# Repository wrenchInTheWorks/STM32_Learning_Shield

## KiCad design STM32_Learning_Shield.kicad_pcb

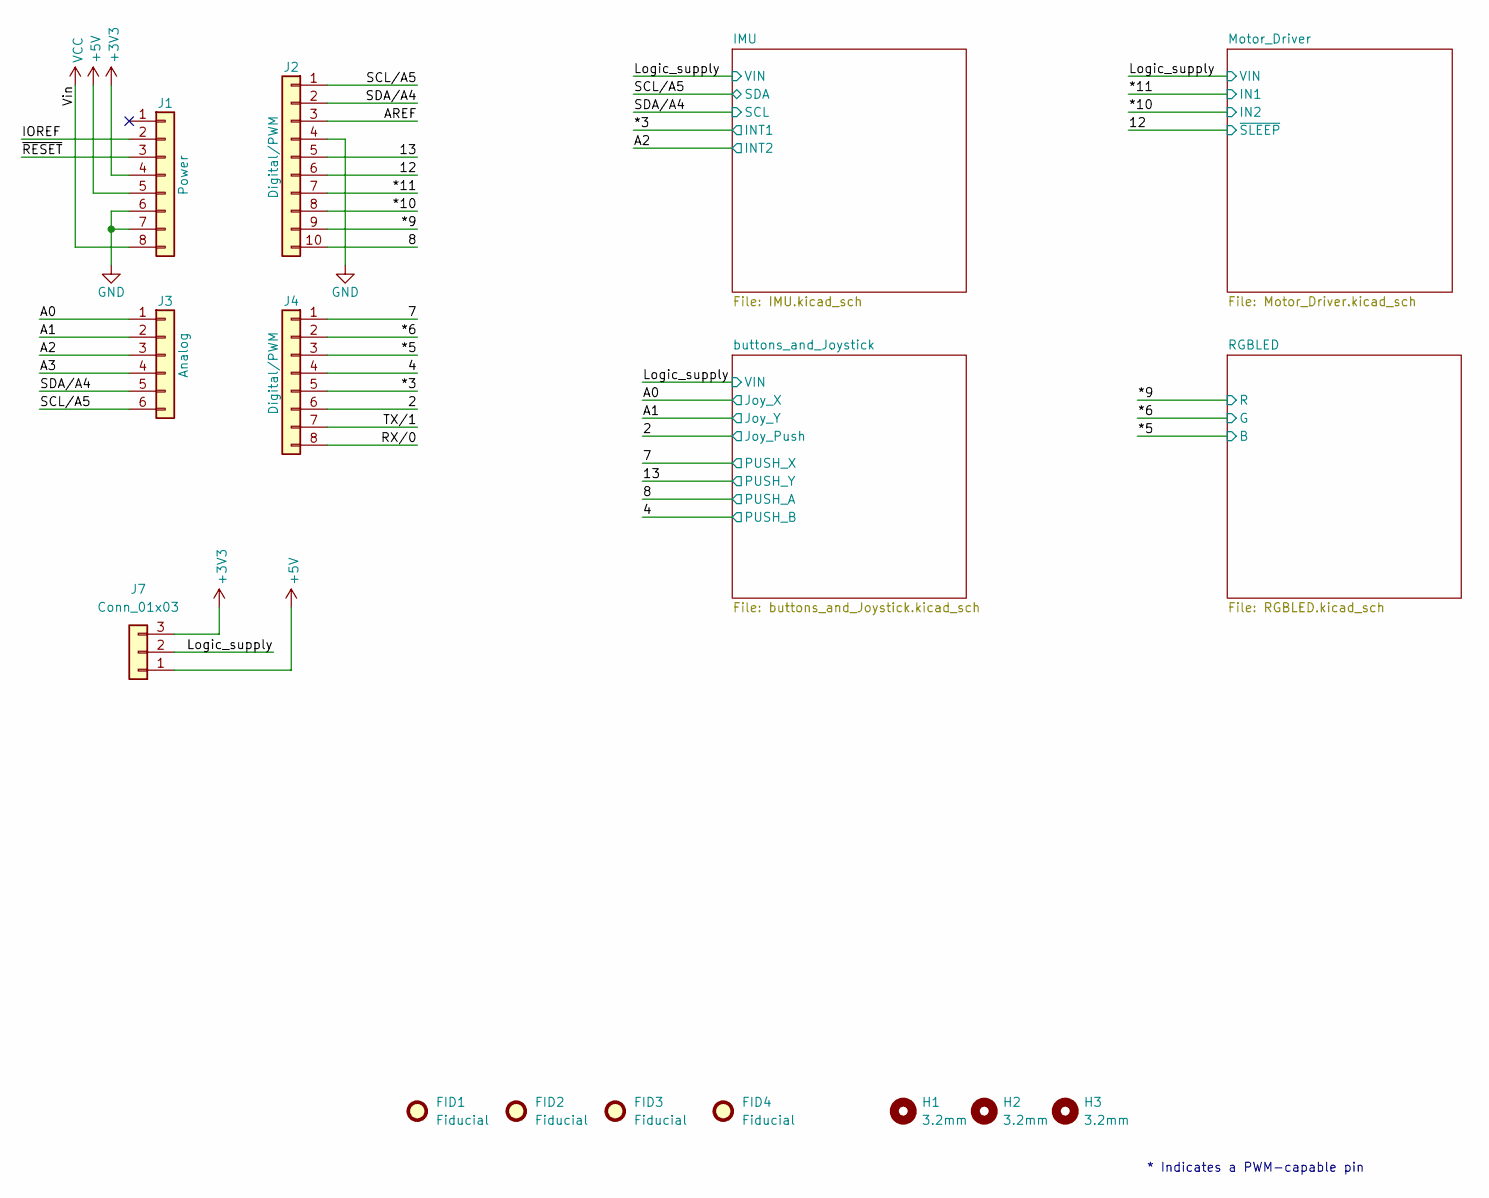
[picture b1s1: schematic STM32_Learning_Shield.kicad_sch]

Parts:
FID1, FID2, FID3, FID4: Fiducial; Fiducial_1mm_Mask3mm
H1, H2, H3: 3.2mm; MountingHole_3.2mm_M3
J1: Power; PinSocket_1x08_P2.54mm_Vertical; MPN PZ254V-11-08P
J2: Digital/PWM; PinSocket_1x10_P2.54mm_Vertical; MPN PZ254V-11-10P
J3: Analog; PinSocket_1x06_P2.54mm_Vertical; MPN HB-PH3-25416PB2GOP
J4: Digital/PWM; PinSocket_1x08_P2.54mm_Vertical; MPN PZ254V-11-08P
J7: Conn_01x03; PinHeader_1x03_P2.54mm_Vertical; MPN 2.54-1*3P

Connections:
+3V3: J1.4, J7.3; also elsewhere on the board
+5V: J1.5, J7.1
/2: J4.6; also elsewhere on the board
/4: J4.4; also elsewhere on the board
/7: J4.1; also elsewhere on the board
/8: J2.10; also elsewhere on the board
/12: J2.6; also elsewhere on the board
/13: J2.5; also elsewhere on the board
/*3: J4.5; also elsewhere on the board
/*5: J4.3; also elsewhere on the board
/*6: J4.2; also elsewhere on the board
/*9: J2.9; also elsewhere on the board
/*10: J2.8; also elsewhere on the board
/*11: J2.7; also elsewhere on the board
/A0: J3.1; also elsewhere on the board
/A1: J3.2; also elsewhere on the board
/A2: J3.3; also elsewhere on the board
/A3: J3.4
/AREF: J2.3
/IOREF: J1.2
/Logic_supply: J7.2; also elsewhere on the board
/RX/0: J4.8
/SCL/A5: J2.1, J3.6; also elsewhere on the board
/SDA/A4: J2.2, J3.5; also elsewhere on the board
/TX/1: J4.7
/~RESET: J1.3
GND: J1.6, J1.7, J2.4; also elsewhere on the board
VCC: J1.8

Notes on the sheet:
* Indicates a PWM-capable pin

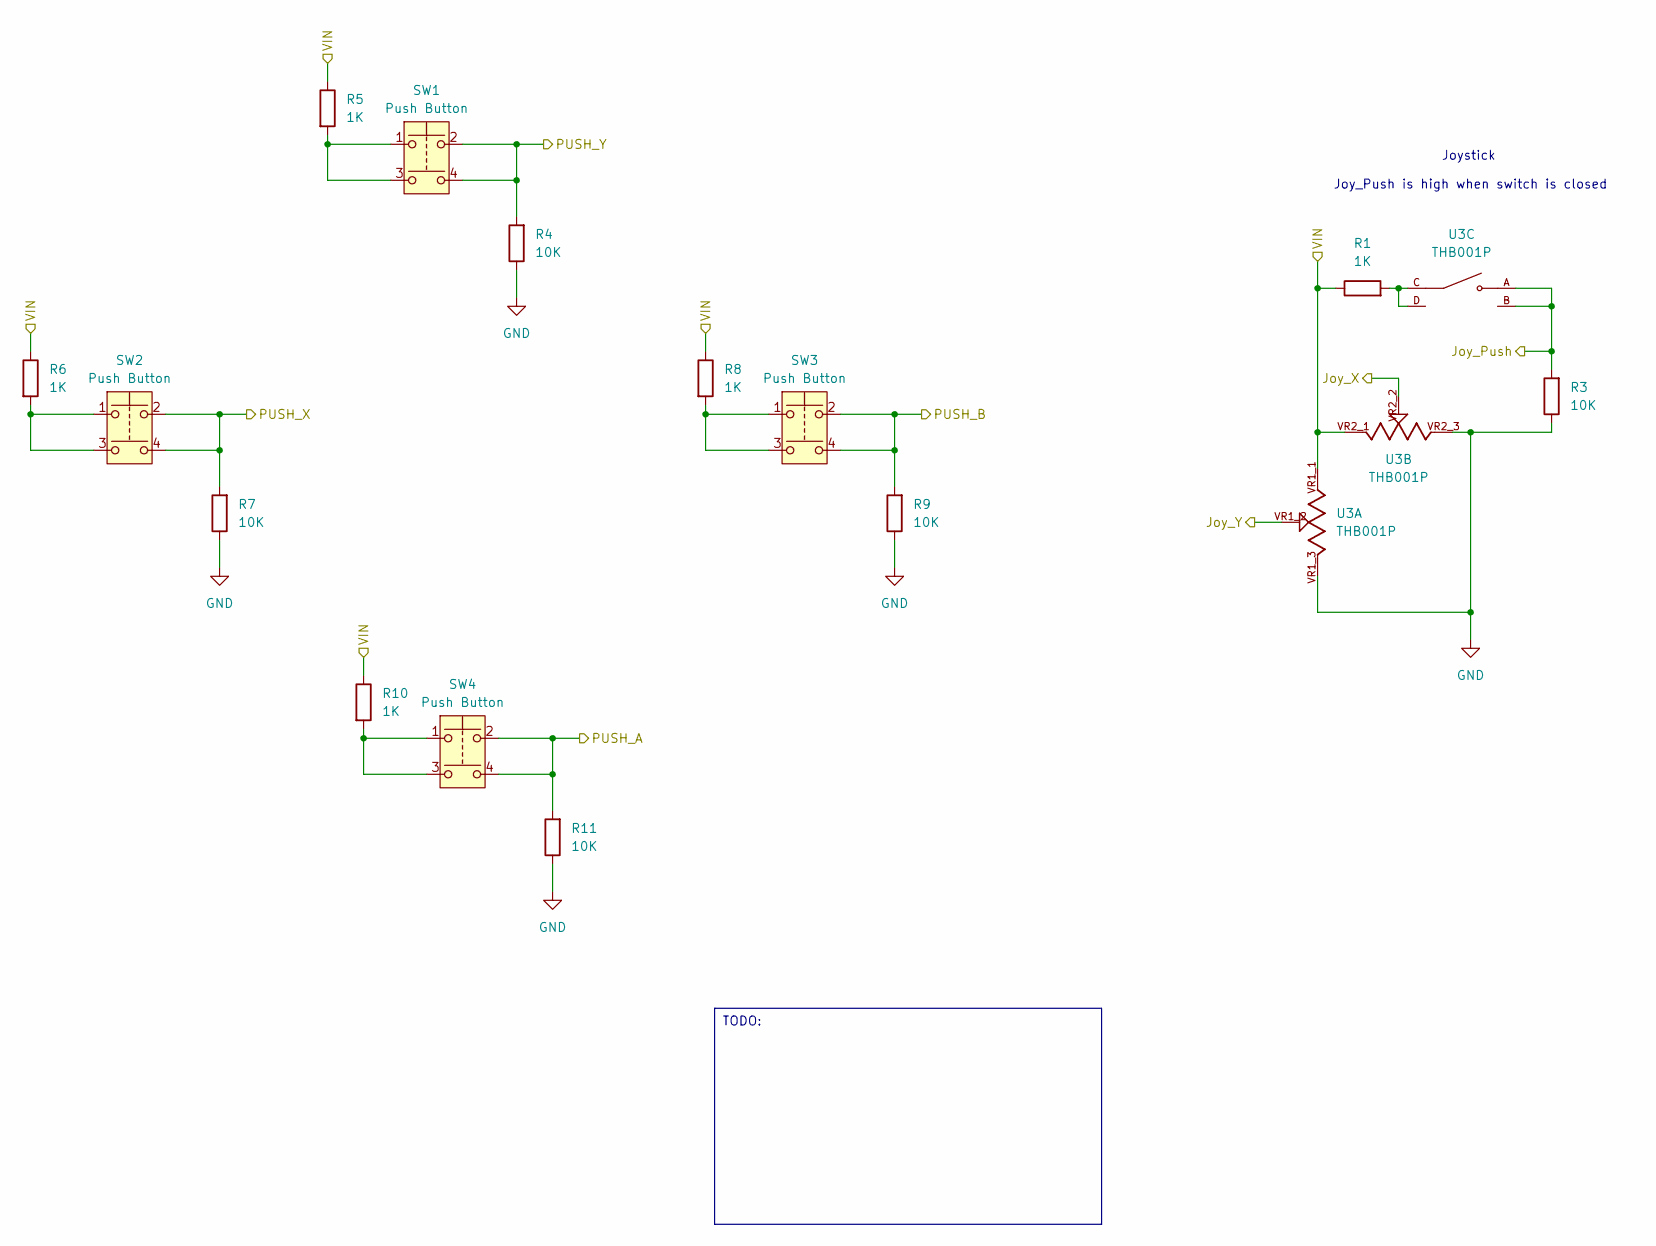
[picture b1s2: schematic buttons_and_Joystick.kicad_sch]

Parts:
R1, R5, R6, R8, R10: 1K; R_0603_1608Metric; MPN 0603WAF1001T5E
R3, R4, R7, R9, R11: 10K; R_0805_2012Metric; MPN 0805W8F1002T5E
SW1, SW2, SW3, SW4: Push Button; SW-TH_4P-L6.0-W6.0-P4.50-LS6.5; MPN TC-00104FB-110E-03
U3: THB001P; CNK_THB001P; PARTREV 27 Jan 22

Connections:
/2: R3.2, U3.A, U3.B; also elsewhere on the board
/4: R9.2, SW3.2, SW3.4; also elsewhere on the board
/7: R7.2, SW2.2, SW2.4; also elsewhere on the board
/8: R11.2, SW4.2, SW4.4; also elsewhere on the board
/13: R4.2, SW1.2, SW1.4; also elsewhere on the board
/A0: U3.VR2_2; also elsewhere on the board
/A1: U3.VR1_2; also elsewhere on the board
/Logic_supply: R1.1, R5.1, R6.1, R8.1, R10.1, U3.VR1_1, U3.VR2_1; also elsewhere on the board
GND: R3.1, R4.1, R7.1, R9.1, R11.1, U3.VR1_3, U3.VR2_3; also elsewhere on the board
unnamed: R1.2, U3.C, U3.D
unnamed: R5.2, SW1.1, SW1.3
unnamed: R6.2, SW2.1, SW2.3
unnamed: R8.2, SW3.1, SW3.3
unnamed: R10.2, SW4.1, SW4.3

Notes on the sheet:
TODO:
Joy_Push is high when switch is closed
Joystick

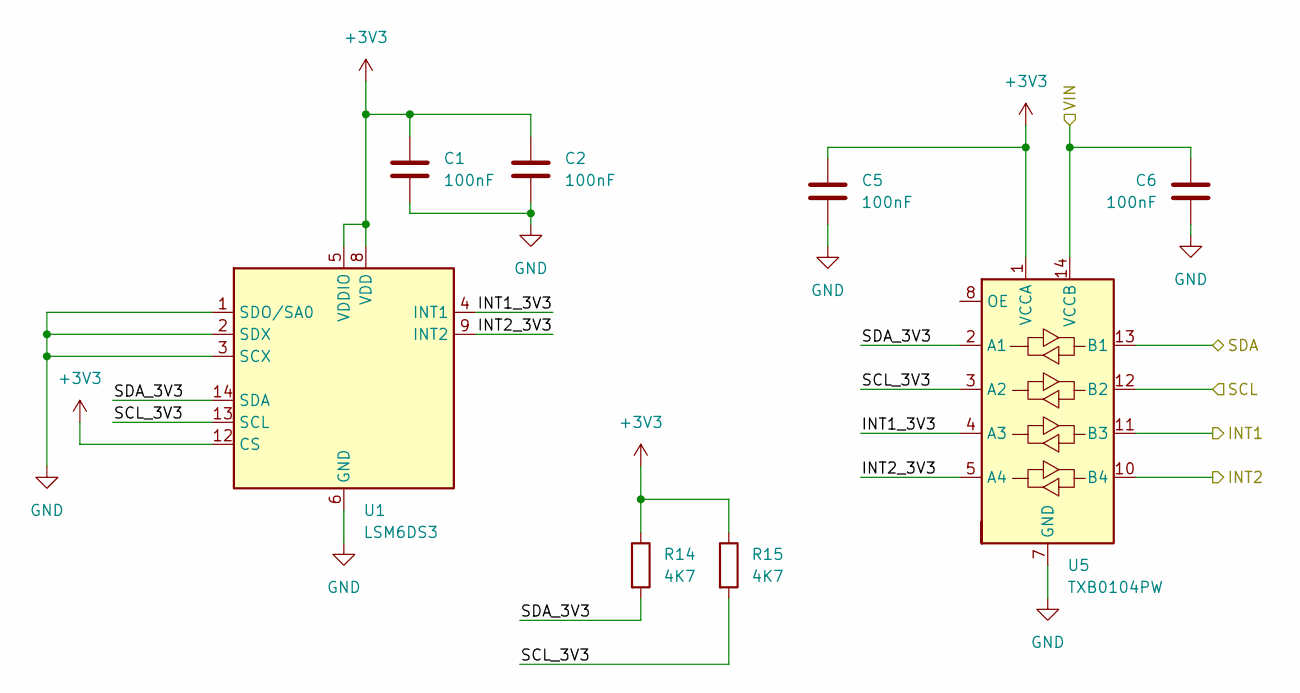
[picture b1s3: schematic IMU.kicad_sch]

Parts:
C1, C2, C5, C6: 100nF; C_0603_1608Metric; MPN CL10B104KB8NNNC
R14, R15: 4K7; R_0603_1608Metric; MPN 0603WAF4701T5E
U1: LSM6DS3; LGA-14_3x2.5mm_P0.5mm_LayoutBorder3x4y; MPN LSM6DS3TR-C
U5: TXB0104PW; SOIC-14_3.9x8.7mm_P1.27mm; MPN TXB0104PWR

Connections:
+3V3: C1.1, C2.1, C5.1, R14.1, R15.1, U1.5 (VDDIO), U1.8 (VDD), U1.12 (CS), U5.1 (VCCA); also elsewhere on the board
/*3: U5.11 (B3); also elsewhere on the board
/A2: U5.10 (B4); also elsewhere on the board
/IMU/INT1_3V3: U1.4 (INT1), U5.4 (A3)
/IMU/INT2_3V3: U1.9 (INT2), U5.5 (A4)
/IMU/SCL_3V3: R15.2, U1.13 (SCL), U5.3 (A2)
/IMU/SDA_3V3: R14.2, U1.14 (SDA), U5.2 (A1)
/Logic_supply: C6.1, U5.14 (VCCB); also elsewhere on the board
/SCL/A5: U5.13 (B1); also elsewhere on the board
/SDA/A4: U5.12 (B2); also elsewhere on the board
GND: C1.2, C2.2, C5.2, C6.2, U1.1 (SDO/SA0), U1.2 (SDX), U1.3 (SCX), U1.6 (GND), U1.7 (GND), U5.7 (GND); also elsewhere on the board

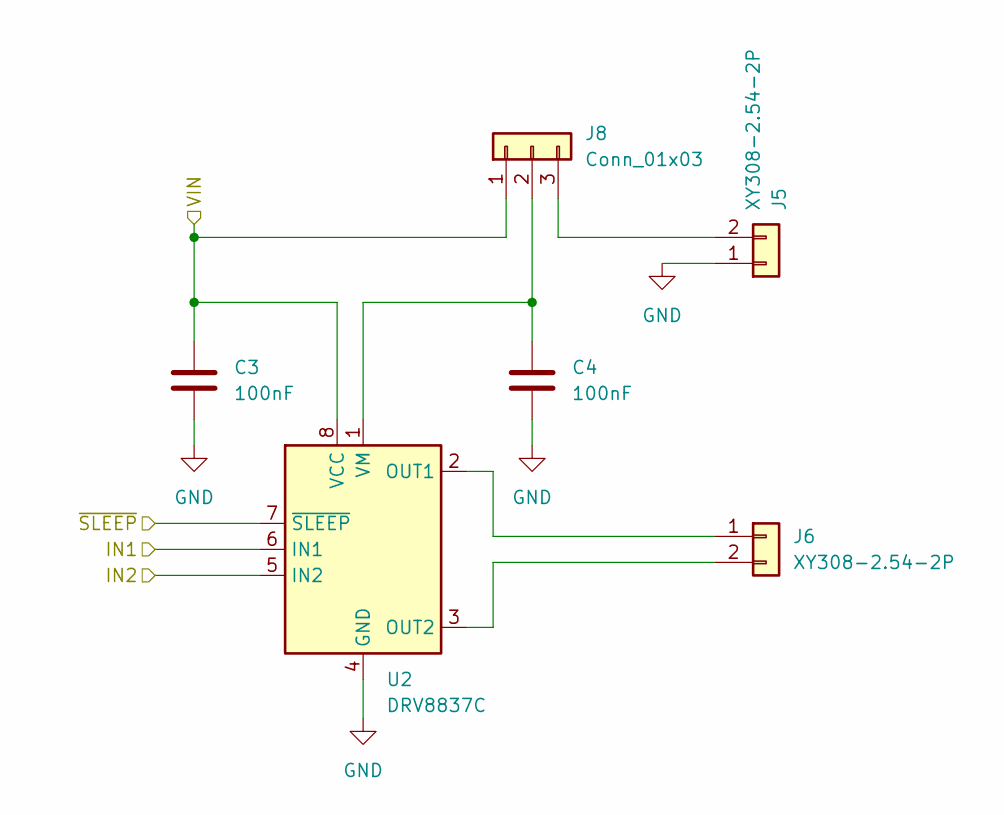
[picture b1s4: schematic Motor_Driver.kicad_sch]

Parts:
C3, C4: 100nF; C_0603_1608Metric; MPN CL10B104KB8NNNC
J5, J6: XY308-2.54-2P; TerminalBlock_Xinya_XY308-2.54-2P_1x02_P2.54mm_Horizontal; MPN XY308-2.54-2P
J8: Conn_01x03; PinHeader_1x03_P2.54mm_Vertical; MPN 2.54-1*3P
U2: DRV8837C; WSON-8-1EP_2x2mm_P0.5mm_EP0.9x1.6mm; MPN DRV8837CDSGR

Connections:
/12: U2.7 (~SLEEP); also elsewhere on the board
/*10: U2.5 (IN2); also elsewhere on the board
/*11: U2.6 (IN1); also elsewhere on the board
/Logic_supply: C3.1, J8.1, U2.8 (VCC); also elsewhere on the board
GND: C3.2, C4.2, J5.1, U2.4 (GND), U2.9 (GND); also elsewhere on the board
unnamed: J5.2, J8.3
unnamed: J6.1, U2.2 (OUT1)
unnamed: J6.2, U2.3 (OUT2)
unnamed: C4.1, J8.2, U2.1 (VM)

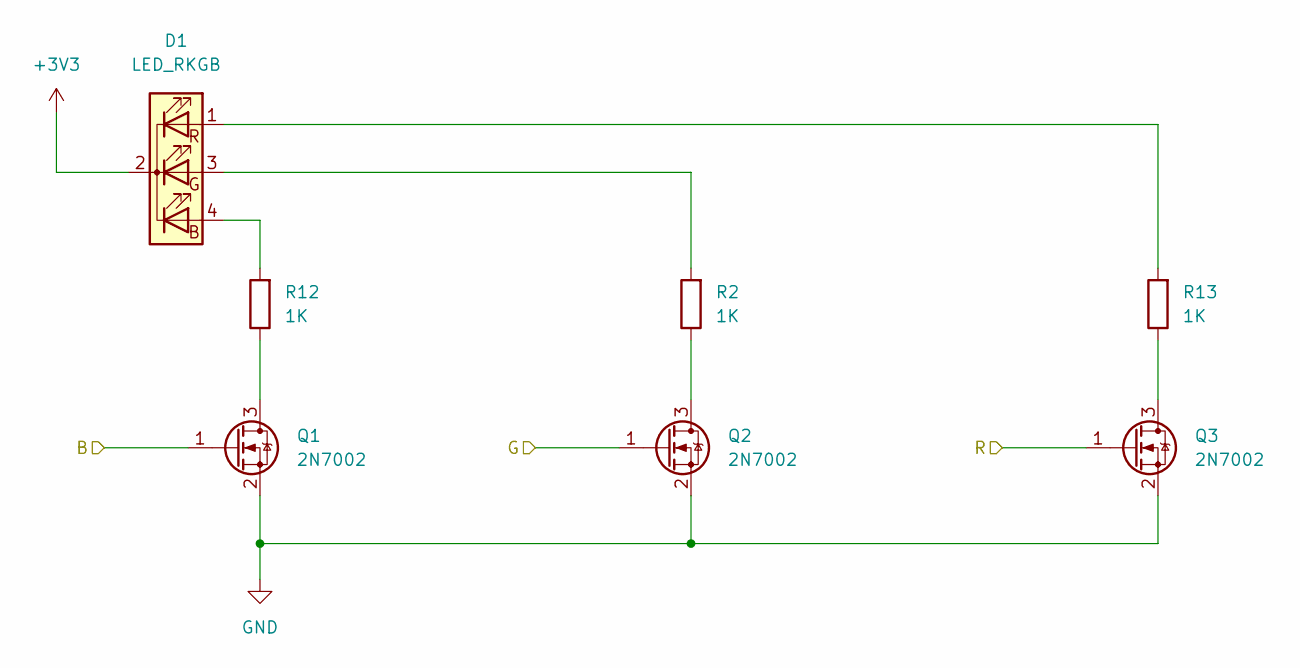
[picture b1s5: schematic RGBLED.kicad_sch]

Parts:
D1: LED_RKGB; LED_D5.0mm-4_RGB; MPN TJ-L5FPTXHMCSLCRGB-A5
Q1, Q2, Q3: 2N7002; SOT-23; MPN 2N7002
R2, R12, R13: 1K; R_0603_1608Metric; MPN 0603WAF1001T5E

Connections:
+3V3: D1.2 (K); also elsewhere on the board
/*5: Q1.1 (G); also elsewhere on the board
/*6: Q2.1 (G); also elsewhere on the board
/*9: Q3.1 (G); also elsewhere on the board
GND: Q1.2 (S), Q2.2 (S), Q3.2 (S); also elsewhere on the board
unnamed: D1.4 (BA), R12.2
unnamed: D1.3 (GA), R2.2
unnamed: D1.1 (RA), R13.2
unnamed: Q1.3 (D), R12.1
unnamed: Q2.3 (D), R2.1
unnamed: Q3.3 (D), R13.1

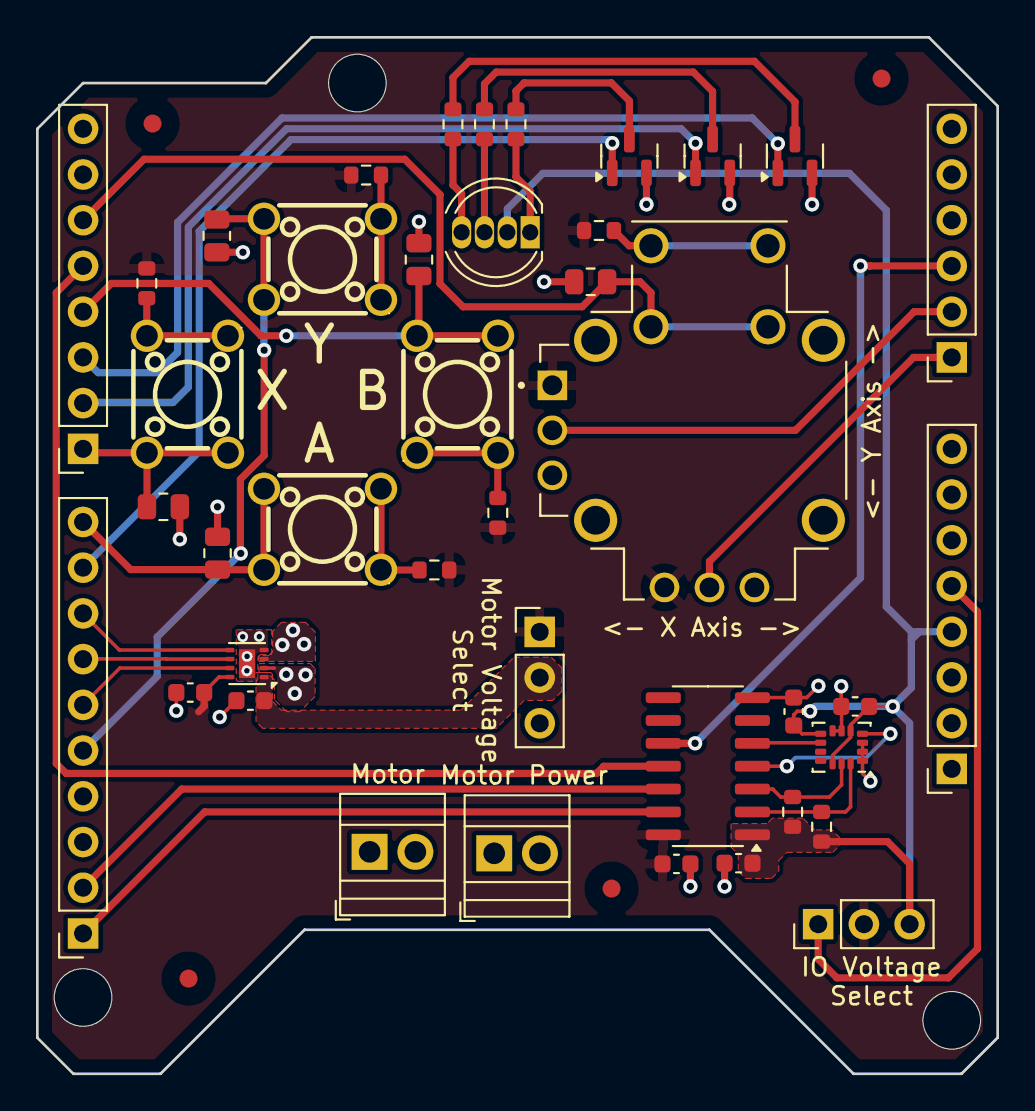
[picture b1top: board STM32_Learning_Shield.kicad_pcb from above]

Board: 2 copper layers, 53.3 x 57.6 mm, 48 parts (0 on the bottom side), 40 nets.

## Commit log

2025-01-16 Completed First layout
2025-02-19 Add Fiducials
